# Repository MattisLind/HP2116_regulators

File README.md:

# HP2116_regulators
A project to create replicas of the two voltage regulator boards of the HP2116.

Unfortunately my HP 2116B which I was able to rescue from destruction in the fall of 2025 was missing not just two logic boards (of which one I was able to buy on Ebay later) but also two very important small regulator boards. The purpose of these two boards is to control the generation of all the voltages needed by the computer.

Finding the exact boards will probably take quite long time if at all possible.

A fellow collector took photos of the boards in his HP 2116C machine. They are very similar except for the memorys regulator not supplying a 32V so those components are not populated.

He also took some measurements of the boards

Thank you Jack! With this I will be able to create boards that fit the machine correctly.

I will be facing a number of problems when doing this. For example there are extensive use of really old Germanium transistors used. The reason for this is partly because of the low Vbe forward voltage. These transistors are used in the current sense circuit basically sitting with the B and E over the current sense resistor. The start to conduct over 0.2V and thus limiting or shutting down the power supply if there are excess current. This circuit with these specifcations wouldn't work with Silicon transistors.

Then the Logic Regulator board are using the Fairchild CTL chip family for logic functions and sequencing of the voltages in the power supply. I thought about replacing it with a corresponding TTL circuit but then the problem is that I don't really now how the TTL circuit react when low voltages are used. I.e. when the power supply is starting up. CTL is basically emitter coupled logic and I came to the conclusion that it would be possible to replicate the functionality using discrete NPN and PNP transistors. Tieing together the emitters of PNP transistors creates AND gates while tieing togther emitters of NPN transistors creates OR gates.

I simulated this design in LTSpice and came to the conclusion that it will likely work as the original circuit using the integrated CTL chip.

The waveforms of the power monitor

Green is the simulated +32V. Delayed and then goes out after about 2 seconds. Blue is the +12V that power up slowly. Red is the even slower -22V. The cyan signal is the 4.5V PSO signal that tells is there is a overheating condition. The resulting signal is the violet. It enables the -12V regulator when low and shuts it down when grounded. It looks like the logic is working.

In the picture below green is the signal to the -12V supply and the blue is the 4.5V power line.

Here is the schematic for the logic regulator.

And this is the memory regulator schematic.

At this point I have started to procure components. I managed to find the 2N1304 and 2N1305 germanium transistors from a vendor in the UK and the same company also had the 2N4044 matched pairs so now all the small resistors, zeners and caps need to be ordered and then I can start laying out the PCB. Care has to be taken so there is room for the heatsinks on the TO5. Both boards have a TO66 power transistor where the exact match is hard to find. I think a NPN TIP41 should be just fine since this just a simple emitter follower output stage to increase the drive power.

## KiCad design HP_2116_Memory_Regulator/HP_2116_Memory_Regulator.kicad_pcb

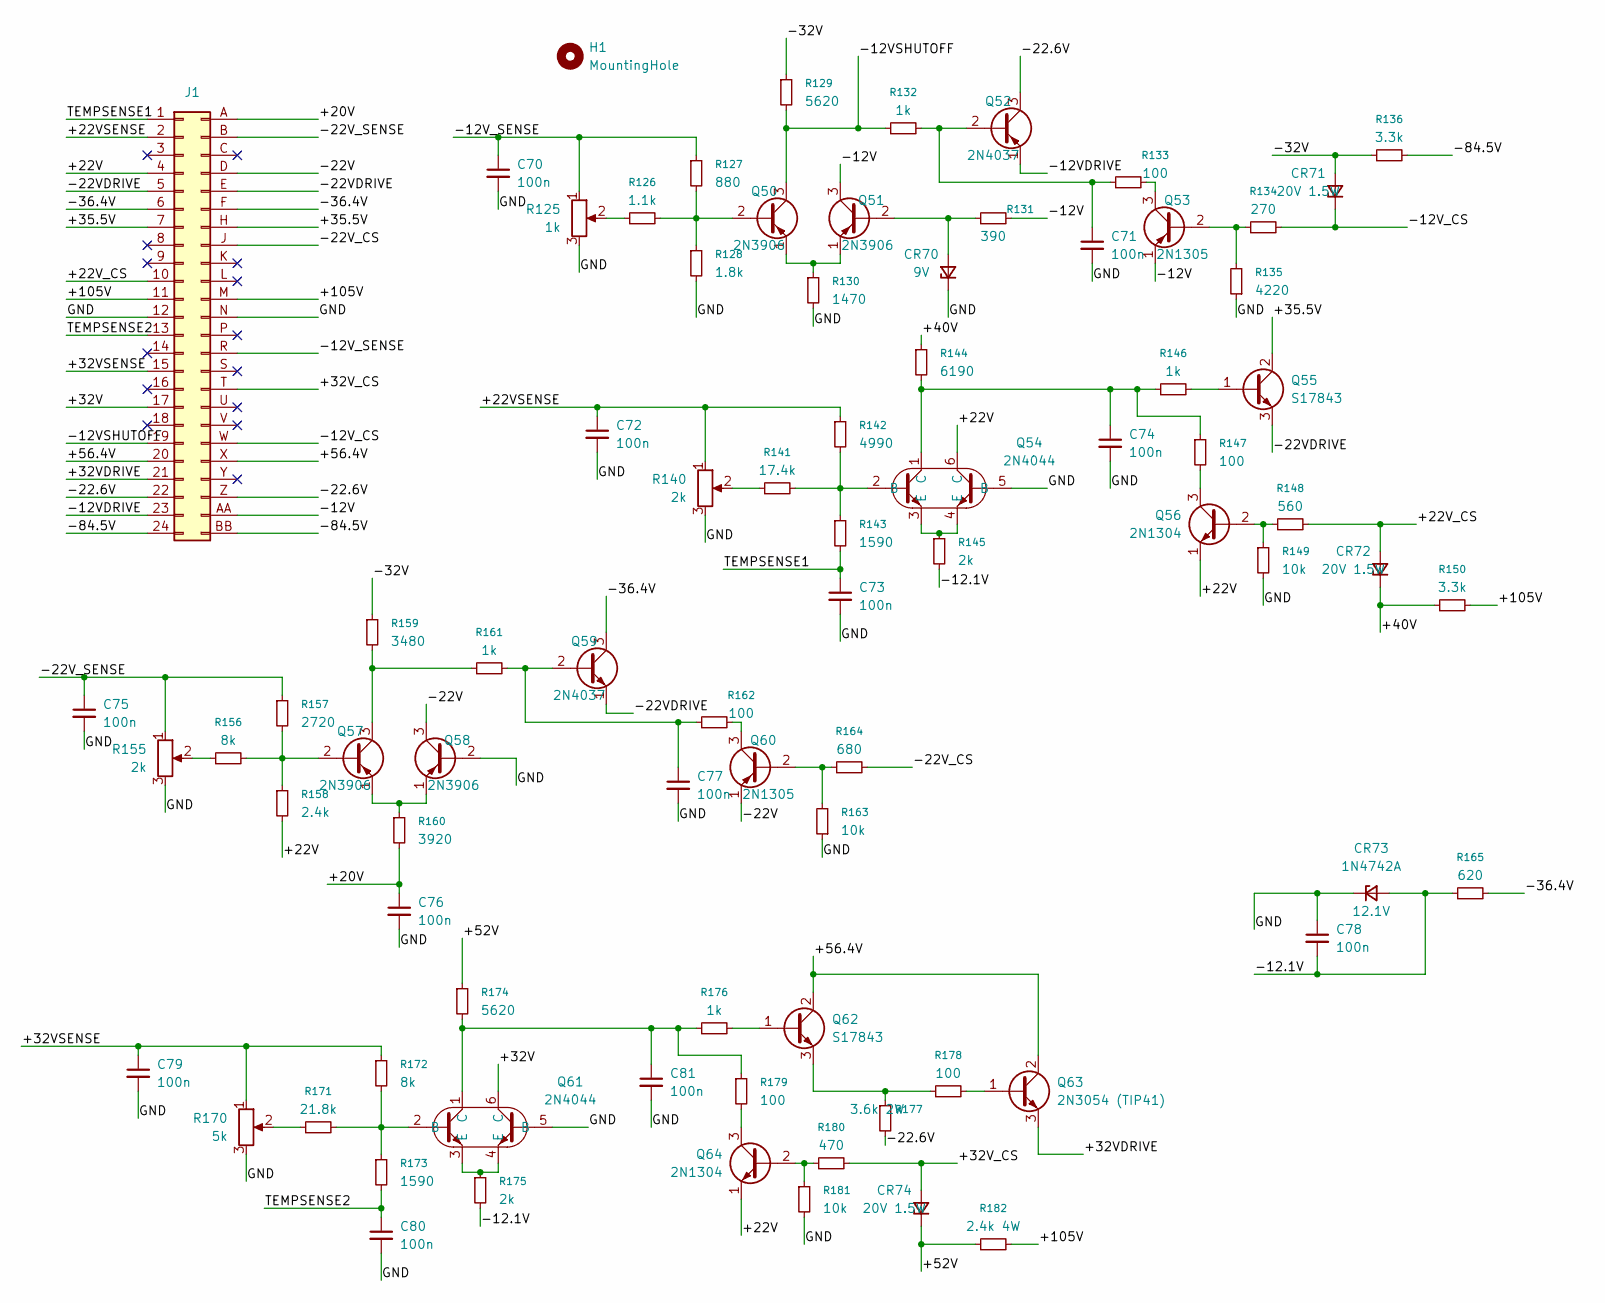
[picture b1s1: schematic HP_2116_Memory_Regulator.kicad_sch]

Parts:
C70, C71, C72, C73, C74, C75, C76, C77, C78, C79, C80, C81: 100n; C_Disc_D4.3mm_W1.9mm_P5.00mm
CR70: 9V; D_DO-41_SOD81_P10.16mm_Horizontal
CR71, CR72, CR74: 20V 1.5W; D_DO-41_SOD81_P10.16mm_Horizontal
CR73: 1N4742A; D_DO-41_SOD81_P10.16mm_Horizontal
H1: MountingHole; MountingHole_3.7mm
J1: Untitled
Q50, Q51, Q57, Q58: 2N3906; TO-92_Inline
Q52, Q59: 2N4037; TO-5-3
Q53, Q60: 2N1305; TO-5-3
Q54, Q61: 2N4044; TO-78-6
Q55, Q62: S17843; TO-5-3
Q56, Q64: 2N1304; TO-5-3
Q63: 2N3054 (TIP41); TO-220-3_Horizontal_TabDown
R125: 1k; Potentiometer_Bourns_3266W_Vertical
R126: 1.1k; R_Axial_DIN0207_L6.3mm_D2.5mm_P10.16mm_Horizontal
R127: 880; R_Axial_DIN0207_L6.3mm_D2.5mm_P10.16mm_Horizontal
R128: 1.8k; R_Axial_DIN0207_L6.3mm_D2.5mm_P10.16mm_Horizontal
R129, R174: 5620; R_Axial_DIN0207_L6.3mm_D2.5mm_P10.16mm_Horizontal
R130: 1470; R_Axial_DIN0207_L6.3mm_D2.5mm_P10.16mm_Horizontal
R131: 390; R_Axial_DIN0207_L6.3mm_D2.5mm_P10.16mm_Horizontal
R132, R146, R161, R176: 1k; R_Axial_DIN0207_L6.3mm_D2.5mm_P10.16mm_Horizontal
R133, R147, R162, R178, R179: 100; R_Axial_DIN0207_L6.3mm_D2.5mm_P10.16mm_Horizontal
R134: 270; R_Axial_DIN0207_L6.3mm_D2.5mm_P10.16mm_Horizontal
R135: 4220; R_Axial_DIN0207_L6.3mm_D2.5mm_P10.16mm_Horizontal
R136, R150: 3.3k; R_Axial_DIN0414_L11.9mm_D4.5mm_P15.24mm_Horizontal
R140, R155: 2k; Potentiometer_Bourns_3266W_Vertical
R141: 17.4k; R_Axial_DIN0207_L6.3mm_D2.5mm_P10.16mm_Horizontal
R142: 4990; R_Axial_DIN0207_L6.3mm_D2.5mm_P10.16mm_Horizontal
R143, R173: 1590; R_Axial_DIN0207_L6.3mm_D2.5mm_P10.16mm_Horizontal
R144: 6190; R_Axial_DIN0207_L6.3mm_D2.5mm_P10.16mm_Horizontal
R145, R175: 2k; R_Axial_DIN0207_L6.3mm_D2.5mm_P10.16mm_Horizontal
R148: 560; R_Axial_DIN0207_L6.3mm_D2.5mm_P10.16mm_Horizontal
R149, R163, R181: 10k; R_Axial_DIN0207_L6.3mm_D2.5mm_P10.16mm_Horizontal
R156, R172: 8k; R_Axial_DIN0207_L6.3mm_D2.5mm_P10.16mm_Horizontal
R157: 2720; R_Axial_DIN0207_L6.3mm_D2.5mm_P10.16mm_Horizontal
R158: 2.4k; R_Axial_DIN0207_L6.3mm_D2.5mm_P10.16mm_Horizontal
R159: 3480; R_Axial_DIN0207_L6.3mm_D2.5mm_P10.16mm_Horizontal
R160: 3920; R_Axial_DIN0207_L6.3mm_D2.5mm_P10.16mm_Horizontal
R164: 680; R_Axial_DIN0207_L6.3mm_D2.5mm_P10.16mm_Horizontal
R165: 620; R_Axial_DIN0414_L11.9mm_D4.5mm_P15.24mm_Horizontal
R170: 5k; Potentiometer_Bourns_3266W_Vertical
R171: 21.8k; R_Axial_DIN0207_L6.3mm_D2.5mm_P10.16mm_Horizontal
R177: 3.6k 2W; R_Axial_DIN0207_L6.3mm_D2.5mm_P10.16mm_Horizontal
R180: 470; R_Axial_DIN0207_L6.3mm_D2.5mm_P10.16mm_Horizontal
R182: 2.4k 4W; R_Axial_DIN0414_L11.9mm_D4.5mm_P25.40mm_Horizontal

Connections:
/+20V: C76.1, J1.A, R160.2
/+22V: J1.4, Q54.6 (C), Q56.1 (E), Q64.1 (E), R158.2
/+22VSENSE: C72.1, J1.2, R140.1, R142.1
/+22V_CS: CR72.2 (A), J1.10, R148.2
/+32V: J1.17, Q61.6 (C)
/+32VDRIVE: J1.21, Q63.3 (E)
/+32VSENSE: C79.1, J1.15, R170.1, R172.1
/+32V_CS: CR74.2 (A), J1.T, R180.2
/+35.5V: J1.7, J1.H, Q55.2 (C)
/+40V: CR72.1 (K), R144.1, R150.1
/+52V: CR74.1 (K), R174.1, R182.1
/+56.4V: J1.20, J1.X, Q62.2 (C), Q63.2 (C)
/+105V: J1.11, J1.M, R150.2, R182.2
/-12.1V: C78.2, CR73.2 (A), R145.2, R165.1, R175.2
/-12V: J1.AA, Q51.3 (C), Q53.1 (E), R131.2
/-12VDRIVE: J1.23, Q52.1 (E)
/-12VSHUTOFF: J1.19, Q50.3 (C), R129.2, R132.1
/-12V_CS: CR71.1 (K), J1.W, R134.2
/-12V_SENSE: C70.1, J1.R, R125.1, R127.1
/-22.6V: J1.22, J1.Z, Q52.3 (C), R177.2
/-22V: J1.D, Q58.3 (C), Q60.1 (E)
/-22VDRIVE: J1.5, J1.E, Q55.3 (E), Q59.1 (E)
/-22V_CS: J1.J, R164.2
/-22V_SENSE: C75.1, J1.B, R155.1, R157.1
/-32V: CR71.2 (A), R129.1, R136.1, R159.1
/-36.4V: J1.6, J1.F, Q59.3 (C), R165.2
/-84.5V: J1.24, J1.BB, R136.2
/GND: C70.2, C71.2, C72.2, C73.2, C74.2, C75.2, C76.2, C77.2, C78.1, C79.2, C80.2, C81.2, CR70.1 (K), CR73.1 (K), J1.12, J1.N, Q54.5 (B), Q58.2 (B), Q61.5 (B), R125.3, R128.2, R130.2, R135.1, R140.3, R149.2, R155.3, R163.1, R170.3, R181.2
/TEMPSENSE1: C73.1, J1.1, R143.2
/TEMPSENSE2: C80.1, J1.13, R173.2
unnamed: C74.1, Q54.1 (C), R144.2, R146.1, R147.1
unnamed: C81.1, Q61.1 (C), R174.2, R176.1, R179.1
unnamed: CR70.2 (A), Q51.2 (B), R131.1
unnamed: Q50.2 (B), R126.2, R127.2, R128.1
unnamed: Q50.1 (E), Q51.1 (E), R130.1
unnamed: C71.1, Q52.2 (B), R132.2, R133.1
unnamed: Q53.2 (B), R134.1, R135.2
unnamed: Q53.3 (C), R133.2
unnamed: Q54.2 (B), R141.2, R142.2, R143.1
unnamed: Q54.3 (E), Q54.4 (E), R145.1
unnamed: Q55.1 (B), R146.2
unnamed: Q56.2 (B), R148.1, R149.1
unnamed: Q56.3 (C), R147.2
unnamed: Q57.2 (B), R156.2, R157.2, R158.1
unnamed: Q57.3 (C), R159.2, R161.1
unnamed: Q57.1 (E), Q58.1 (E), R160.1
unnamed: C77.1, Q59.2 (B), R161.2, R162.1
unnamed: Q60.2 (B), R163.2, R164.1
unnamed: Q60.3 (C), R162.2
unnamed: Q61.2 (B), R171.2, R172.2, R173.1
unnamed: Q61.3 (E), Q61.4 (E), R175.1
unnamed: Q62.1 (B), R176.2
unnamed: Q62.3 (E), R177.1, R178.1
unnamed: Q63.1 (B), R178.2
unnamed: Q64.2 (B), R180.1, R181.1
unnamed: Q64.3 (C), R179.2
unnamed: R125.2, R126.1
unnamed: R140.2, R141.1
unnamed: R155.2, R156.1
unnamed: R170.2, R171.1

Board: 2 copper layers, 81 parts (0 on the bottom side), 60 nets, no tracks yet.

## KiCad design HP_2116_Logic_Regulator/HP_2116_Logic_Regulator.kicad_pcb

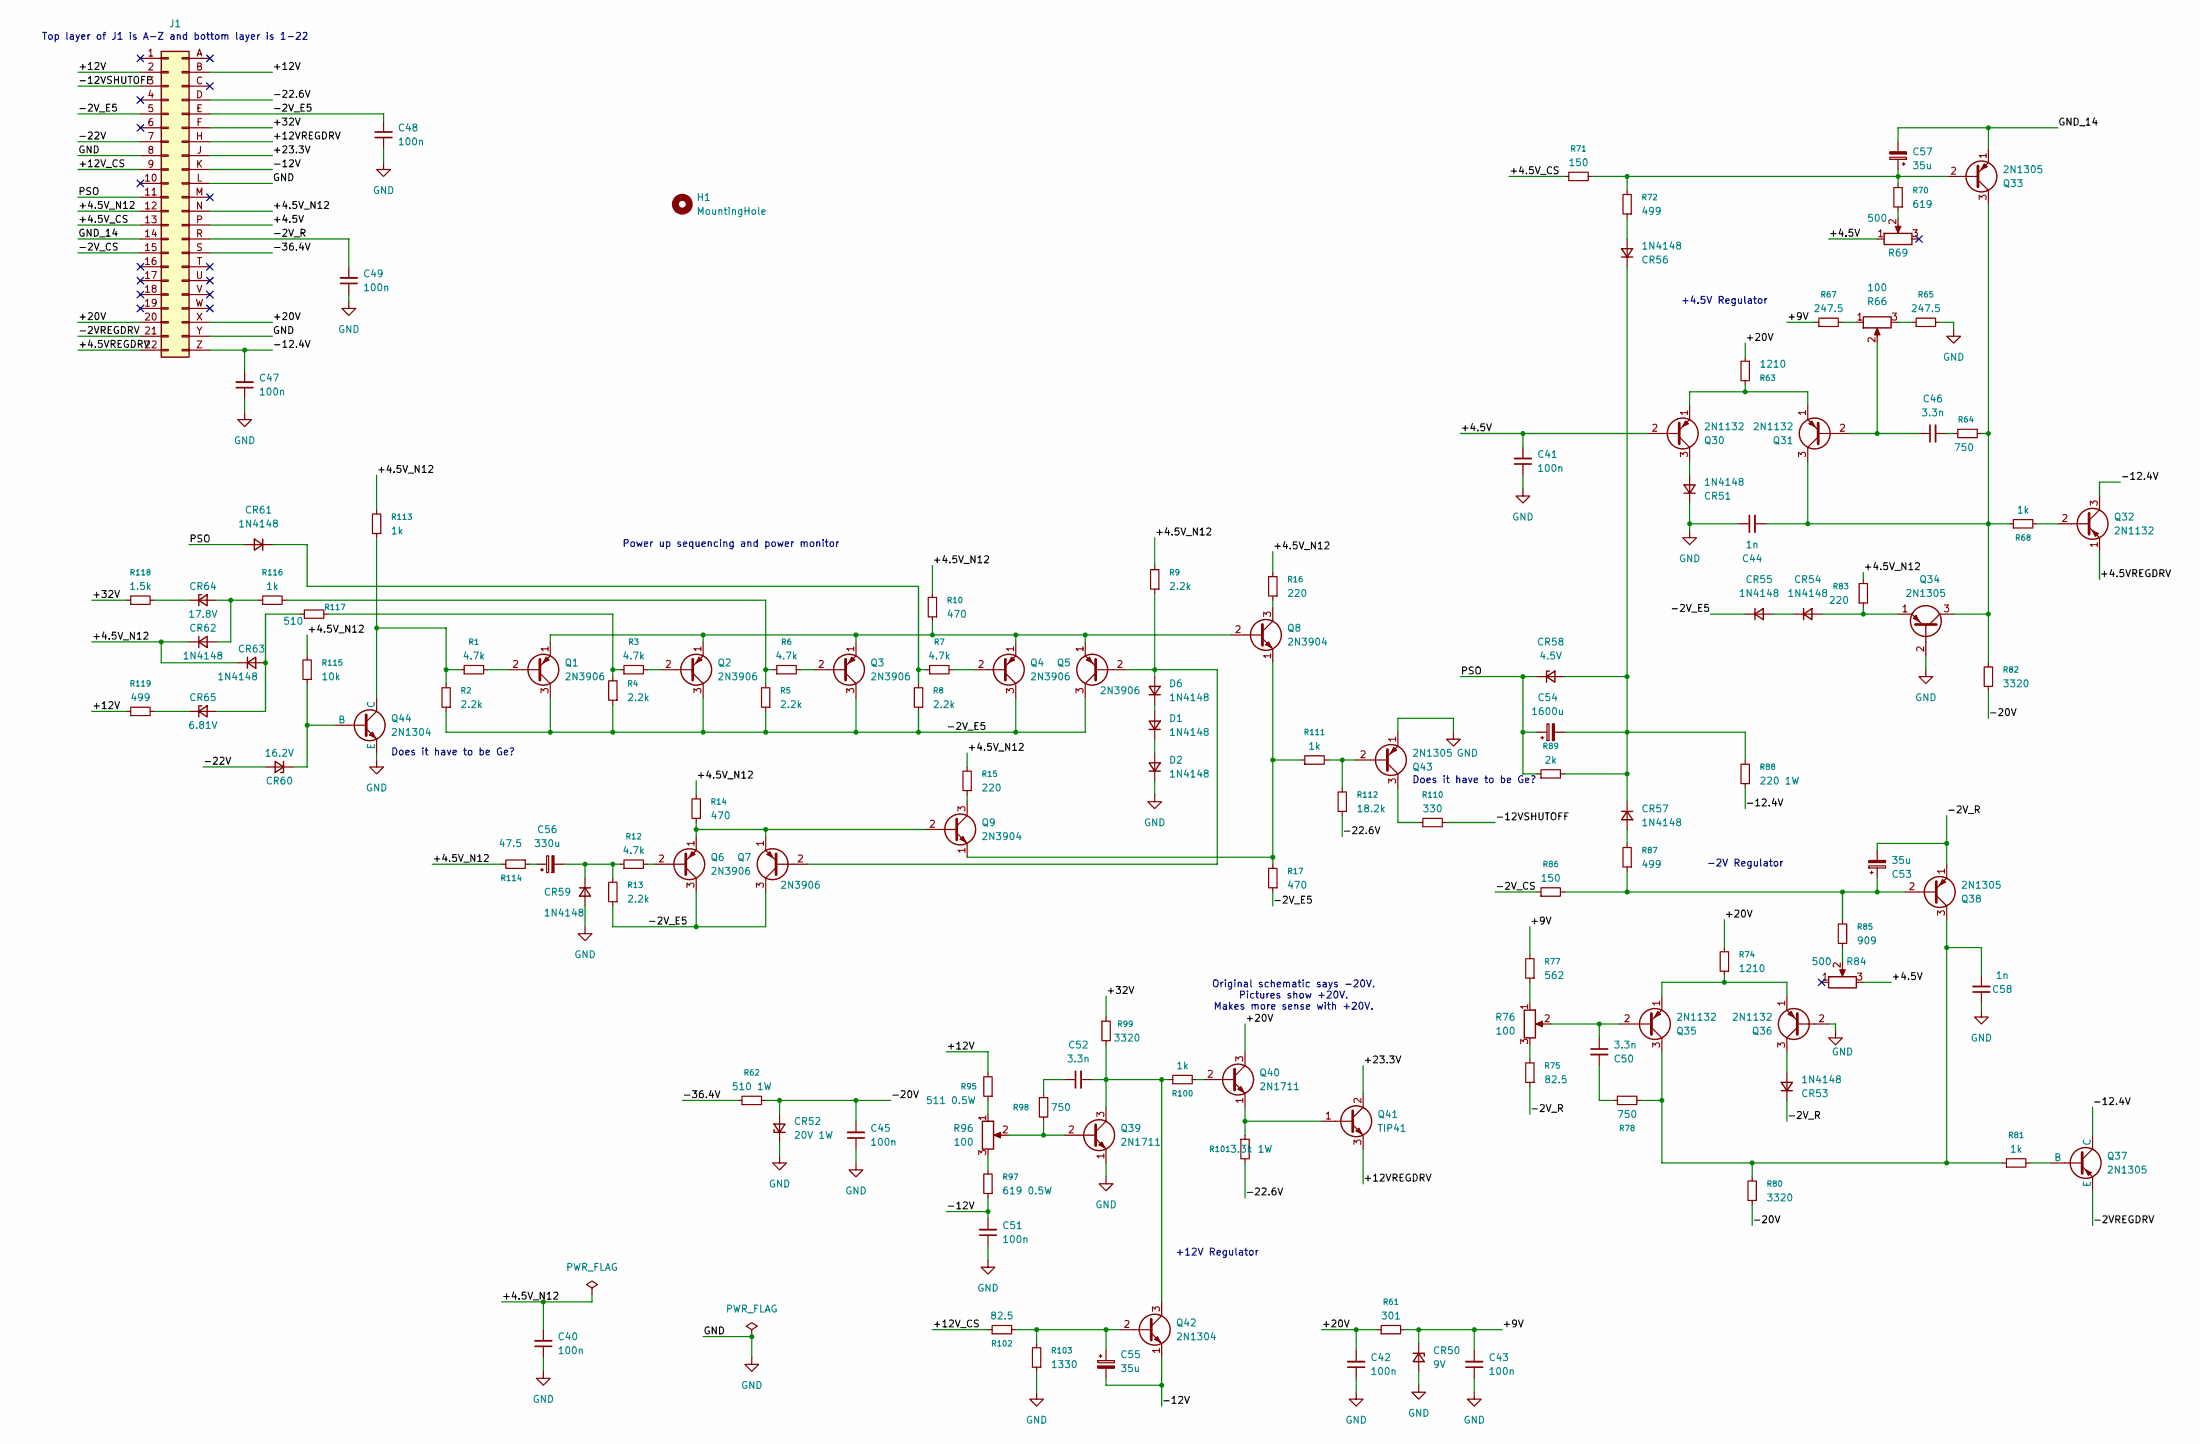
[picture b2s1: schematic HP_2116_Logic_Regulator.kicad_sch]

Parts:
C40, C41, C42, C43, C45, C47, C48, C49, C51: 100n; C_Disc_D4.3mm_W1.9mm_P5.00mm
C44, C58: 1n; C_Disc_D4.3mm_W1.9mm_P5.00mm
C46, C50, C52: 3.3n; C_Disc_D4.3mm_W1.9mm_P5.00mm
C53, C55, C57: 35u; CP_Radial_D5.0mm_P2.00mm
C54: 1600u; CP_Radial_D16.0mm_P7.50mm
C56: 330u; CP_Radial_D6.3mm_P2.50mm
CR50: 9V; D_DO-41_SOD81_P10.16mm_Horizontal
CR51, CR53, CR54, CR55, CR56, CR57, CR59, CR61, CR62, CR63: 1N4148; D_DO-35_SOD27_P10.16mm_Horizontal
CR52: 20V 1W; D_DO-41_SOD81_P10.16mm_Horizontal
CR58: 4.5V; D_DO-35_SOD27_P10.16mm_Horizontal
CR60: 16.2V; D_DO-35_SOD27_P10.16mm_Horizontal
CR64: 17.8V; D_DO-35_SOD27_P10.16mm_Horizontal
CR65: 6.81V; D_DO-35_SOD27_P10.16mm_Horizontal
D1, D2, D6: 1N4148; D_DO-35_SOD27_P10.16mm_Horizontal
H1: MountingHole; MountingHole_3.7mm
J1: 22 Pin HP EDAC
Q1, Q2, Q3, Q4, Q5, Q6, Q7: 2N3906; TO-92_Inline
Q8, Q9: 2N3904; TO-92_Inline
Q30, Q31, Q32, Q35, Q36: 2N1132; TO-5-3
Q33, Q34, Q37, Q38, Q43: 2N1305; TO-5-3
Q39, Q40: 2N1711; TO-5-3
Q41: TIP41; TO-220-3_Horizontal_TabDown
Q42, Q44: 2N1304; TO-5-3
R1, R3, R6, R7, R12: 4.7k; R_Axial_DIN0207_L6.3mm_D2.5mm_P10.16mm_Horizontal
R2, R4, R5, R8, R9, R13: 2.2k; R_Axial_DIN0207_L6.3mm_D2.5mm_P10.16mm_Horizontal
R10, R14, R17: 470; R_Axial_DIN0207_L6.3mm_D2.5mm_P10.16mm_Horizontal
R15, R16, R83: 220; R_Axial_DIN0207_L6.3mm_D2.5mm_P10.16mm_Horizontal
R61: 301; R_Axial_DIN0207_L6.3mm_D2.5mm_P10.16mm_Horizontal
R62: 510 1W; R_Axial_DIN0414_L11.9mm_D4.5mm_P20.32mm_Horizontal
R63, R74: 1210; R_Axial_DIN0207_L6.3mm_D2.5mm_P10.16mm_Horizontal
R64, R78, R98: 750; R_Axial_DIN0207_L6.3mm_D2.5mm_P10.16mm_Horizontal
R65, R67: 247.5; R_Axial_DIN0207_L6.3mm_D2.5mm_P10.16mm_Horizontal
R66, R76, R96: 100; Potentiometer_Bourns_3266W_Vertical
R68, R81, R100, R111, R113, R116: 1k; R_Axial_DIN0207_L6.3mm_D2.5mm_P10.16mm_Horizontal
R69, R84: 500; Potentiometer_Bourns_3266W_Vertical
R70: 619; R_Axial_DIN0207_L6.3mm_D2.5mm_P10.16mm_Horizontal
R71, R86: 150; R_Axial_DIN0207_L6.3mm_D2.5mm_P10.16mm_Horizontal
R72, R87, R119: 499; R_Axial_DIN0207_L6.3mm_D2.5mm_P10.16mm_Horizontal
R75, R102: 82.5; R_Axial_DIN0207_L6.3mm_D2.5mm_P10.16mm_Horizontal
R77: 562; R_Axial_DIN0207_L6.3mm_D2.5mm_P10.16mm_Horizontal
R80, R82, R99: 3320; R_Axial_DIN0207_L6.3mm_D2.5mm_P10.16mm_Horizontal
R85: 909; R_Axial_DIN0207_L6.3mm_D2.5mm_P10.16mm_Horizontal
R88: 220 1W; R_Axial_DIN0414_L11.9mm_D4.5mm_P20.32mm_Horizontal
R89: 2k; R_Axial_DIN0207_L6.3mm_D2.5mm_P10.16mm_Horizontal
R95: 511 0.5W; R_Axial_DIN0309_L9.0mm_D3.2mm_P15.24mm_Horizontal
R97: 619 0.5W; R_Axial_DIN0309_L9.0mm_D3.2mm_P15.24mm_Horizontal
R101: 3.3k 1W; R_Axial_DIN0414_L11.9mm_D4.5mm_P20.32mm_Horizontal
R103: 1330; R_Axial_DIN0207_L6.3mm_D2.5mm_P10.16mm_Horizontal
R110: 330; R_Axial_DIN0207_L6.3mm_D2.5mm_P10.16mm_Horizontal
R112: 18.2k; R_Axial_DIN0207_L6.3mm_D2.5mm_P10.16mm_Horizontal
R114: 47.5; R_Axial_DIN0207_L6.3mm_D2.5mm_P10.16mm_Horizontal
R115: 10k; R_Axial_DIN0207_L6.3mm_D2.5mm_P10.16mm_Horizontal
R117: 510; R_Axial_DIN0207_L6.3mm_D2.5mm_P10.16mm_Horizontal
R118: 1.5k; R_Axial_DIN0207_L6.3mm_D2.5mm_P10.16mm_Horizontal

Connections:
/+4.5V: C41.2, J1.P, Q30.2 (B), R69.1, R84.3
/+4.5VREGDRV: J1.22, Q32.1 (E)
/+4.5V_CS: J1.13, R71.1
/+4.5V_N12: C40.2, CR62.1 (K), CR63.1 (K), J1.12, J1.N, R9.2, R10.2, R14.2, R15.2, R16.2, R83.2, R113.2, R114.2, R115.2
/+9V: C43.2, CR50.1 (K), R61.2, R67.1, R77.2
/+12V: J1.2, J1.B, R95.2, R119.1
/+12VREGDRV: J1.H, Q41.3 (E)
/+12V_CS: J1.9, R102.1
/+20V: C42.2, J1.20, J1.X, Q40.3 (C), R61.1, R63.1, R74.2
/+23.3V: J1.J, Q41.2 (C)
/+32V: J1.F, R99.1, R118.1
/-2VREGDRV: J1.21, Q37.3 (E)
/-2V_CS: J1.15, R86.1
/-2V_E5: C48.2, CR55.1 (K), J1.5, J1.E, Q1.3 (C), Q2.3 (C), Q3.3 (C), Q4.3 (C), Q5.3 (C), Q6.3 (C), Q7.3 (C), R2.1, R4.1, R5.1, R8.1, R13.1, R17.1
/-2V_R: C49.2, C53.2, CR53.1 (K), J1.R, Q38.1 (E), R75.1
/-12.4V: C47.2, J1.Z, Q32.3 (C), Q37.1 (C), R88.1
/-12V: C51.2, C55.2, J1.K, Q42.1 (E), R97.1
/-12VSHUTOFF: J1.3, R110.2
/-20V: C45.2, CR52.2 (A), R62.2, R80.1, R82.1
/-22.6V: J1.D, R101.2, R112.1
/-22V: CR60.2 (A), J1.7
/-36.4V: J1.S, R62.1
/GND_14: C57.2, J1.14, Q33.1 (E)
/PSO: C54.1, CR58.1 (K), CR61.2 (A), J1.11, R89.1
GND: C40.1, C41.1, C42.1, C43.1, C44.1, C45.1, C47.1, C48.1, C49.1, C51.1, C58.1, CR50.2 (A), CR51.1 (K), CR52.1 (K), CR59.2 (A), D2.1 (K), J1.8, J1.L, J1.Y, Q34.2 (B), Q36.2 (B), Q39.1 (E), Q43.1 (E), Q44.3 (E), R65.2, R103.1
unnamed: C46.2, R64.2
unnamed: C50.2, R78.1
unnamed: C52.1, R98.1
unnamed: C56.1, R114.1
unnamed: CR51.2 (A), Q30.3 (C)
unnamed: CR53.2 (A), Q36.3 (C)
unnamed: CR54.2 (A), Q34.1 (E), R83.1
unnamed: CR54.1 (K), CR55.2 (A)
unnamed: CR56.2 (A), R72.1
unnamed: C54.2, CR56.1 (K), CR57.1 (K), CR58.2 (A), R88.2, R89.2
unnamed: CR57.2 (A), R87.2
unnamed: C56.2, CR59.1 (K), R12.1, R13.2
unnamed: CR60.1 (K), Q44.2 (B), R115.1
unnamed: CR61.1 (K), R7.1, R8.2
unnamed: CR62.2 (A), CR64.2 (A), R116.1
unnamed: CR63.2 (A), CR65.2 (A), R117.1
unnamed: CR64.1 (K), R118.2
unnamed: CR65.1 (K), R119.2
unnamed: D1.2 (A), D6.1 (K)
unnamed: D1.1 (K), D2.2 (A)
unnamed: D6.2 (A), Q5.2 (B), Q7.2 (B), R9.1
unnamed: Q1.2 (B), R1.2
unnamed: Q1.1 (E), Q2.1 (E), Q3.1 (E), Q4.1 (E), Q5.1 (E), Q8.2 (B), R10.1
unnamed: Q2.2 (B), R3.2
unnamed: Q3.2 (B), R6.2
unnamed: Q4.2 (B), R7.2
unnamed: Q6.2 (B), R12.2
unnamed: Q6.1 (E), Q7.1 (E), Q9.2 (B), R14.1
unnamed: Q8.3 (C), R16.1
unnamed: Q8.1 (E), Q9.1 (E), R17.2, R111.1
unnamed: Q9.3 (C), R15.1
unnamed: Q30.1 (E), Q31.1 (E), R63.2
unnamed: C46.1, Q31.2 (B), R66.2
unnamed: C44.2, Q31.3 (C), Q33.3 (C), Q34.3 (C), R64.1, R68.1, R82.2
unnamed: Q32.2 (B), R68.2
unnamed: C57.1, Q33.2 (B), R70.2, R71.2, R72.2
unnamed: C50.1, Q35.2 (B), R76.2
unnamed: C58.2, Q35.3 (C), Q38.3 (C), R78.2, R80.2, R81.1
unnamed: Q35.1 (E), Q36.1 (E), R74.1
unnamed: Q37.2 (B), R81.2
unnamed: C53.1, Q38.2 (B), R85.2, R86.2, R87.1
unnamed: Q39.2 (B), R96.2, R98.2
unnamed: C52.2, Q39.3 (C), Q42.3 (C), R99.2, R100.1
unnamed: Q40.2 (B), R100.2
unnamed: Q40.1 (E), Q41.1 (B), R101.1
unnamed: C55.1, Q42.2 (B), R102.2, R103.2
unnamed: Q43.2 (B), R111.2, R112.2
unnamed: Q43.3 (C), R110.1
unnamed: Q44.1 (C), R1.1, R2.2, R113.1
unnamed: R65.1, R66.3
unnamed: R66.1, R67.2
unnamed: R69.2, R70.1
unnamed: R75.2, R76.3
unnamed: R76.1, R77.1
unnamed: R84.2, R85.1
unnamed: R95.1, R96.1
unnamed: R96.3, R97.2
unnamed: R5.2, R6.1, R116.2
unnamed: R3.1, R4.2, R117.2

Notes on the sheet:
Does it have to be Ge?
Original schematic says -20V. Pictures show +20V. Makes more sense with +20V.
Top layer of J1 is A-Z and bottom layer is 1-22
+4.5V Regulator
Power up sequencing and power monitor
+12V Regulator
-2V Regulator

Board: 2 copper layers, 126 parts (0 on the bottom side), 84 nets, no tracks yet.

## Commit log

2026-04-03 Adding kicad projects.
2026-04-03 Missing regulator picture
2026-04-03 Add files
2026-04-03 Enhance README with project details and challenges
    Expanded project description with details about missing components, challenges with using old transistors, and simulation results.
2026-04-04 Added LTspice circuit.
2026-04-04 Updated some values in the logic regulator and re-generated the svg and created pdfs.
2026-04-04 Update README with regulator schematics and procurement info
    Added schematics for logic and memory regulators, and updated component procurement status.
2026-06-14 Started to do a layout.
